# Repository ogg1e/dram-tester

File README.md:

# 41256 and 4164 dram-tester using Arduino Nano

UNTESTED!! Initial revision. 

Arduino Nano DRAM tester for 41256 and 4164

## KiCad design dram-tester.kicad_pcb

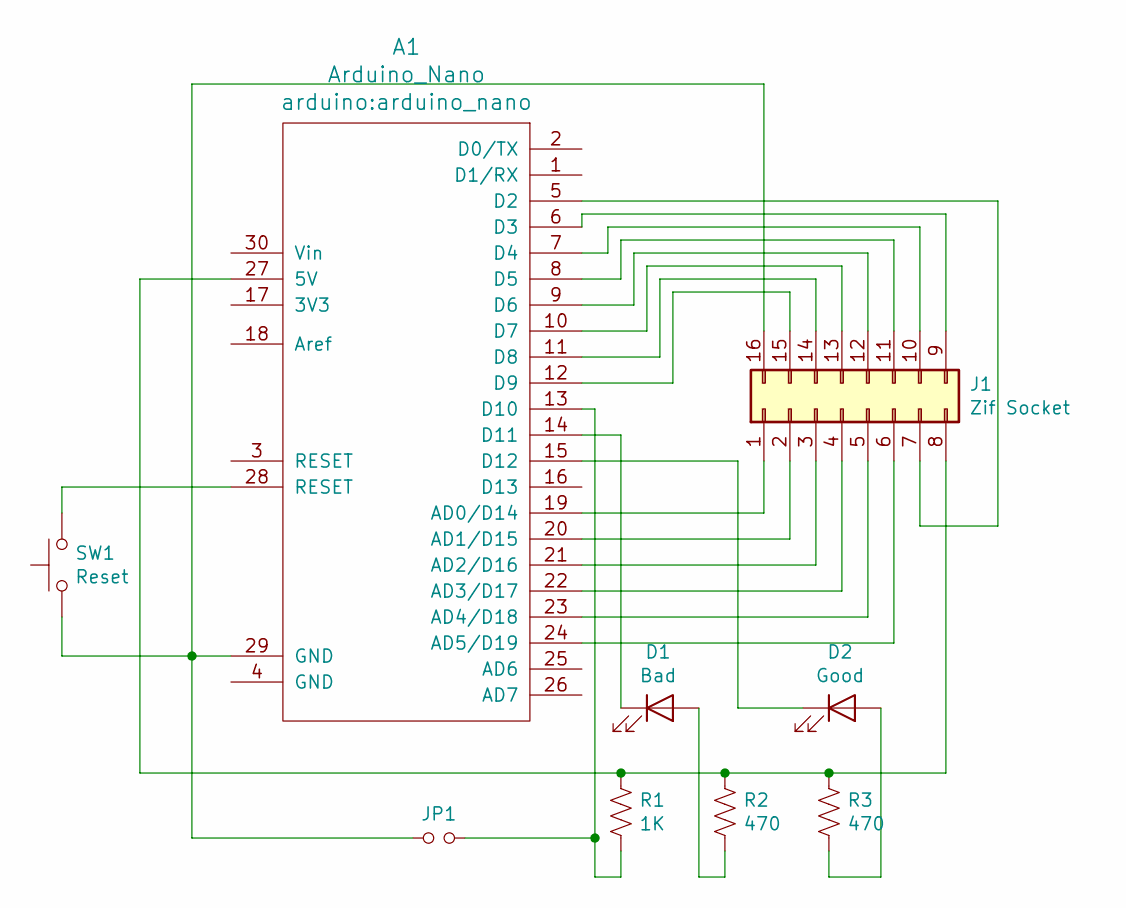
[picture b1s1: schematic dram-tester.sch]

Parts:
A1: Arduino_Nano; arduino_nano
D1: Bad; LED_D5.0mm
D2: Good; LED_D5.0mm
J1: Zif Socket; DIP_Socket-16_W4.3_W5.08_W7.62_W10.16_W10.9_3M_216-3340-00-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
JP1: on=4164,off=41256; Pin_Header_Straight_1x02_Pitch2.54mm
R1: 1K; R_Axial_DIN0207_L6.3mm_D2.5mm_P7.62mm_Horizontal
R2, R3: 470; R_Axial_DIN0207_L6.3mm_D2.5mm_P7.62mm_Horizontal
SW1: Reset; SW_PUSH_6mm

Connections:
unnamed: A1.5 (D2), J1.7
unnamed: A1.6 (D3), J1.9
unnamed: A1.7 (D4), J1.10
unnamed: A1.8 (D5), J1.11
unnamed: A1.9 (D6), J1.12
unnamed: A1.10 (D7), J1.13
unnamed: A1.11 (D8), J1.14
unnamed: A1.12 (D9), J1.15
unnamed: A1.13 (D10), JP1.2, R1.2
unnamed: A1.14 (D11), D1.1 (K)
unnamed: A1.15 (D12), D2.1 (K)
unnamed: A1.19 (AD0/D14), J1.1
unnamed: A1.20 (AD1/D15), J1.2
unnamed: A1.21 (AD2/D16), J1.3
unnamed: A1.22 (AD3/D17), J1.4
unnamed: A1.23 (AD4/D18), J1.5
unnamed: A1.24 (AD5/D19), J1.6
unnamed: A1.27 (5V), J1.8, R1.1, R2.1, R3.1
unnamed: A1.28 (RESET), SW1.2
unnamed: A1.29 (GND), J1.16, JP1.1, SW1.1
unnamed: D1.2 (A), R2.2
unnamed: D2.2 (A), R3.2

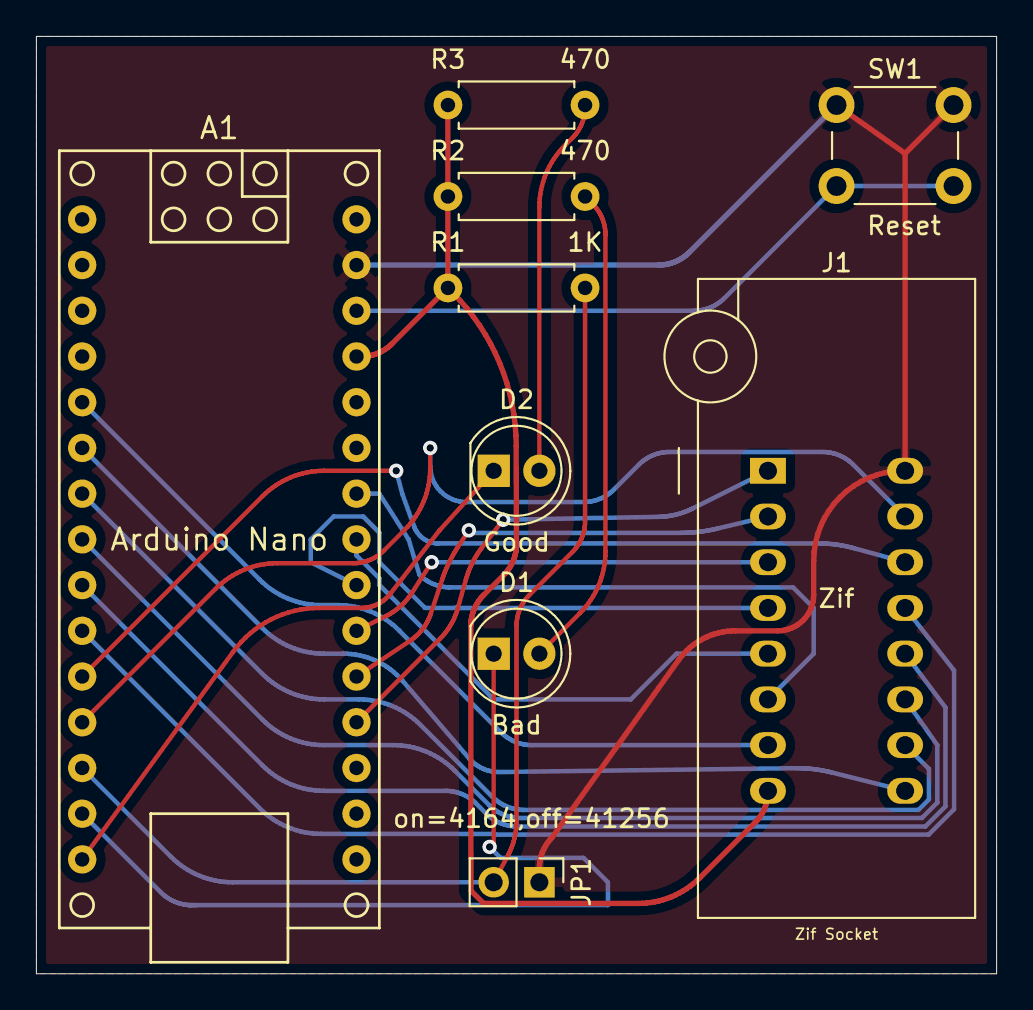
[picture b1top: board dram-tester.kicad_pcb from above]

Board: 2 copper layers, 53.3 x 52.1 mm, 9 parts (0 on the bottom side), 22 nets.

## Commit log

2020-08-21 added ground plane
2020-08-21 cleaned up pcb
2020-12-21 update fix
2020-12-21 Create LICENSE
